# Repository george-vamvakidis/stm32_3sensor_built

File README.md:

# stm32_3sensor_built
An STM32 implementation with 3 sensors (BMP388, MCU-6050 and TMP112). The communication is through I2C and SPI.

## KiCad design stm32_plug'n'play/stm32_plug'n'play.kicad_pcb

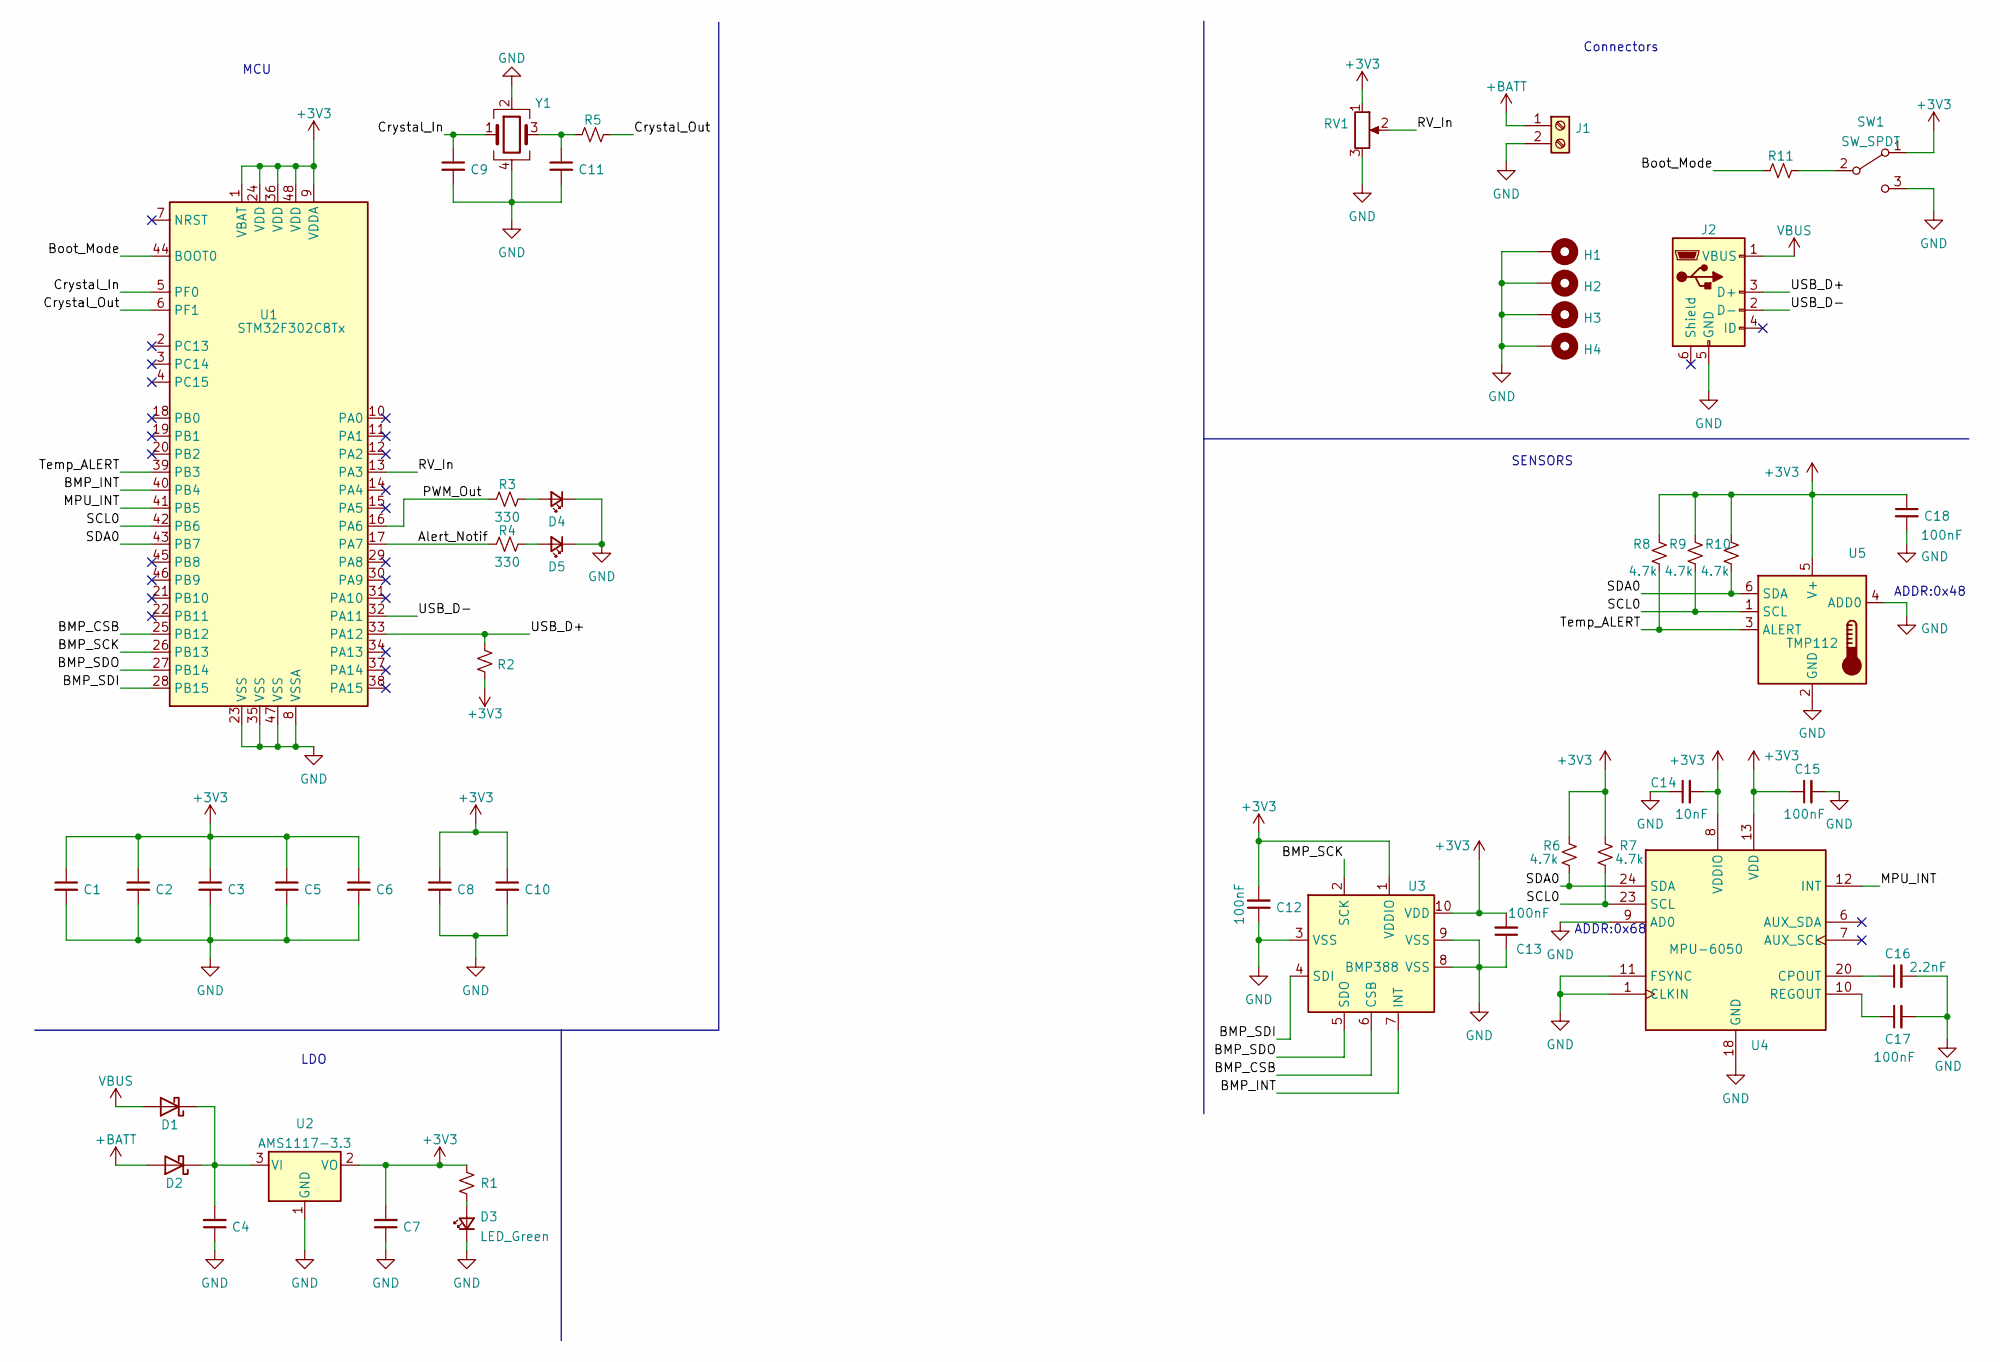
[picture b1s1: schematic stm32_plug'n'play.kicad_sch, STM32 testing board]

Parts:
C1, C2, C3, C5, C8, C12, C13, C15, C17, C18: 100nF; C_0402_1005Metric
C4, C7: 10uF; C_0603_1608Metric
C6: 4.7uF; C_0603_1608Metric
C9, C11: 12pF; C_0402_1005Metric
C10: 1uF; C_0603_1608Metric
C14: 10nF; C_0402_1005Metric
C16: 2.2nF; C_0402_1005Metric
D1, D2: 1N5819; D_SOD-123
D3: LED_Green; LED_0805_2012Metric
D4: LED_Blue; LED_0805_2012Metric
D5: LED_Red; LED_0805_2012Metric
H1, H2, H3, H4: MountingHole_Pad; MountingHole_4.3mm_M4_Pad_Via
J1: Screw_Terminal_01x02; TerminalBlock_Altech_AK300-2_P5.00mm
J2: USB_B_Micro; USB_Micro-B_Wuerth_629105150521
R1, R3, R4: 330; R_0402_1005Metric
R2: 1.5k; R_0402_1005Metric
R5: 47; R_0402_1005Metric
R6, R7, R8, R9, R10: 4.7k; R_0402_1005Metric
R11: 10k; R_0402_1005Metric
RV1: R_Potentiometer; Potentiometer_Alps_RK09K_Single_Horizontal
SW1: SW_SPDT; PinHeader_1x03_P2.54mm_Vertical_SMD_Pin1Left
U1: STM32F302C8Tx; LQFP-48_7x7mm_P0.5mm
U2: AMS1117-3.3; SOT-223-3_TabPin2
U3: BMP388; ST_HLGA-10_2.5x2.5mm_P0.6mm_LayoutBorder3x2y
U4: MPU-6050; InvenSense_QFN-24_4x4mm_P0.5mm
U5: TMP112; SOT-563
Y1: X322516MLB4SI; Crystal_SMD_3225-4Pin_3.2x2.5mm

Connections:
+3V3: C1.1, C2.1, C3.1, C5.1, C6.1, C7.2, C8.1, C10.1, C12.2, C13.2, C14.2, C15.1, C18.1, R1.2, R2.2, R6.1, R7.1, R8.1, R9.1, R10.1, RV1.1, SW1.1 (A), U1.1 (VBAT), U1.9 (VDDA), U1.24 (VDD), U1.36 (VDD), U1.48 (VDD), U2.2 (VO), U3.1 (VDDIO), U3.10 (VDD), U4.8 (VDDIO), U4.13 (VDD), U5.5 (V+)
+BATT: D2.2 (A), J1.1
/Alert_Notif: R4.1, U1.17 (PA7)
/BMP_CSB: U1.25 (PB12), U3.6 (CSB)
/BMP_INT: U1.40 (PB4), U3.7 (INT)
/BMP_SCK: U1.26 (PB13), U3.2 (SCK)
/BMP_SDI: U1.28 (PB15), U3.4 (SDI)
/BMP_SDO: U1.27 (PB14), U3.5 (SDO)
/Boot_Mode: R11.1, U1.44 (BOOT0)
/Crystal_In: C9.1, U1.5 (PF0), Y1.1
/Crystal_Out: R5.2, U1.6 (PF1)
/MPU_INT: U1.41 (PB5), U4.12 (INT)
/PWM_Out: R3.1, U1.16 (PA6)
/RV_In: RV1.2, U1.13 (PA3)
/SCL0: R7.2, R9.2, U1.42 (PB6), U4.23 (SCL), U5.1 (SCL)
/SDA0: R6.2, R10.2, U1.43 (PB7), U4.24 (SDA), U5.6 (SDA)
/Temp_ALERT: R8.2, U1.39 (PB3), U5.3 (ALERT)
/USB_D+: J2.3 (D+), R2.1, U1.33 (PA12)
/USB_D-: J2.2 (D-), U1.32 (PA11)
GND: C1.2, C2.2, C3.2, C4.1, C5.2, C6.2, C7.1, C8.2, C9.2, C10.2, C11.2, C12.1, C13.1, C14.1, C15.2, C16.2, C17.2, C18.2, D3.1 (K), D4.1 (K), D5.1 (K), H1.1, H2.1, H3.1, H4.1, J1.2, J2.5 (GND), RV1.3, SW1.3 (C), U1.8 (VSSA), U1.23 (VSS), U1.35 (VSS), U1.47 (VSS), U2.1 (GND), U3.3 (VSS), U3.8 (VSS), U3.9 (VSS), U4.1 (CLKIN), U4.9 (AD0), U4.11 (FSYNC), U4.18 (GND), U5.2 (GND), U5.4 (ADD0), Y1.2, Y1.4; also elsewhere on the board
unnamed: C4.2, D1.1 (K), D2.1 (K), U2.3 (VI)
unnamed: C11.1, R5.1, Y1.3
unnamed: C16.1, U4.20 (CPOUT)
unnamed: C17.1, U4.10 (REGOUT)
unnamed: D3.2 (A), R1.1
unnamed: D4.2 (A), R3.2
unnamed: D5.2 (A), R4.2
unnamed: R11.2, SW1.2 (B)
VBUS: D1.2 (A), J2.1 (VBUS)

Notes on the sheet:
MCU
LDO
ADDR:0x48
ADDR:0x68
Connectors
SENSORS

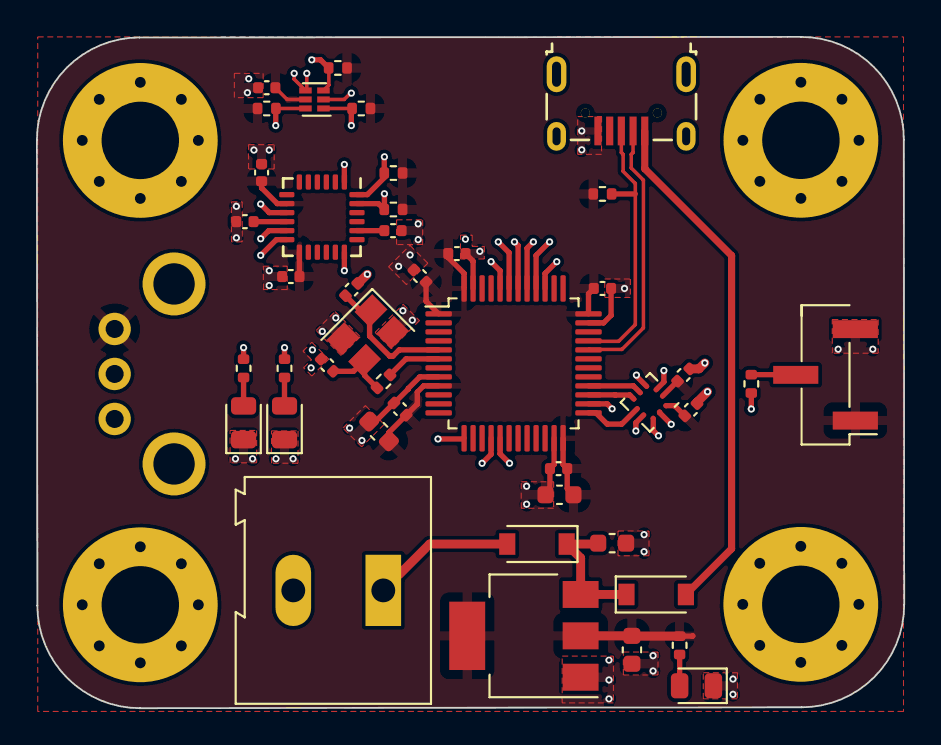
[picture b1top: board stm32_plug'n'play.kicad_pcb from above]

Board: 4 copper layers, 48.2 x 37.3 mm, 48 parts (0 on the bottom side), 29 nets.

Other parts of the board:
H4#2, H4#3, H4#4: MountingHole_Pad; MountingHole_4.3mm_M4_Pad_Via

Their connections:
GND: H4#2.1, H4#3.1, H4#4.1; also elsewhere on the board
